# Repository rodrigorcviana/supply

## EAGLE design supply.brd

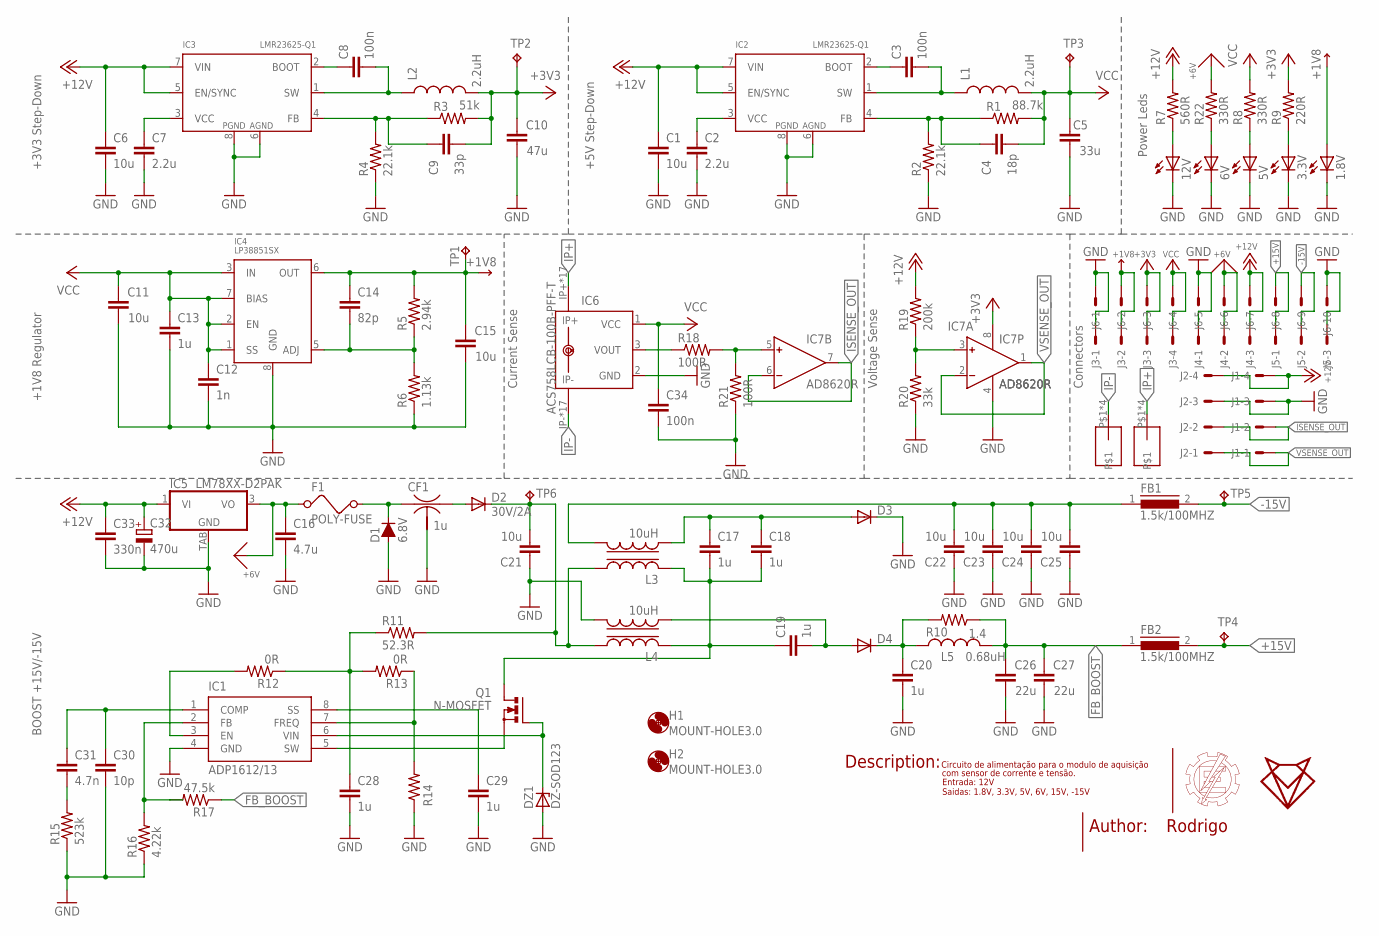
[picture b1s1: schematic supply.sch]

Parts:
1.8V, 3.3V, 5V, 6V, 12V: LEDCHIP-LED0805; CHIP-LED0805
C1, C6, C11, C15, C21, C22, C23, C24, C25: 10u; C1206
C2, C7: 2.2u; C0805
C3, C8: 100n; C0805
C4: 18p; C0805
C5: 33u; C1206
C9: 33p; C0805
C10: 47u; C1206
C12: 1n; C0805
C13, C17, C18: 1u; C0805
C14: 82p; C0805
C16: 4.7u; C0805
C19, C20, C28, C29: 1u; C0603
C26, C27: 22u; C1206
C30: 10p; C0603
C31: 4.7n; C0603
C32: 470u; 150CLZ-0810
C33: 330n; C0603
C34: 100n; C0603
CF1: 1u; NFM21C
D1: 6.8V; SMB
D2: 30V/2A; SOD123
D3, D4: DIODE-SOD323-W; SOD323-W
DZ1: DZ-SOD123; SOD123
F1: POLY-FUSE; 1210
FB1, FB2: 1.5k/100MHZ; 0603
H1, H2: MOUNT-HOLE3.0; 3,0
IC1: ADP1612/13; 8-MSOP
IC2, IC3: LMR23625-Q1; SO08
IC4: LP38851SX; TO263-7
IC5: LM78XX-D2PAK; TO263-3
IC6: ACS758LCB-100B-PFF-T; CB-PFF
IC7: AD8620R; SO8
J1: 22-05-7048-04; 7395-04
J2, J3: 22-27-2041-04; 6410-04
J4, J5: 22-27-2031-03; 6410-03
J6: 22-05-7108-10; 7395-10
L1, L2: 2.2uH; L-NR3010
L3, L4: 10uH; MSD7342-SMD
L5: 0.68uH; L2012C
Q1: N-MOSFET; SOT23
R1: 88.7k; R0603
R2, R4: 22.1k; R0603
R3: 51k; R0603
R5: 2.94k; R0603
R6: 1.13k; R0603
R7: 560R; R0603
R8, R22: 330R; R0603
R9: 220R; R0603
R10: 1.4; R0603
R11: 52.3R; R0603
R12, R13: 0R; R0603
R14: R-US_R0603; R0603
R15: 523k; R0603
R16: 4.22k; R0603
R17: 47.5k; R0603
R18, R21: 100R; R0805
R19: 200k; R0805
R20: 33k; R0805
TP1, TP2, TP3, TP4, TP5, TP6: TPPAD1-13; P1-13
U$3, U$4: SCREWCONECTOR

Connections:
+1V8: 1.8V.A, C14.1, C15.2, IC4.6 (OUT), J3.2, J6.2, R5.2, TP1.TP
+3V3: C9.2, C10.2, IC7.8 (V+), J3.3, J6.3, L2.P$2 (2), R3.2, R9.2, TP2.TP
+6V: C16.1, F1.1, IC5.3 (VO), J4.2, J6.6, R22.2
+12V: C1.1, C6.1, C32.+, C33.1, IC2.5 (EN/SYNC), IC2.7 (VIN), IC3.5 (EN/SYNC), IC3.7 (VIN), IC5.1 (VI), J1.4, J2.4, J4.3, J6.7, R7.2, R19.2
+15V: FB2.2, J5.1, J6.8, TP4.TP
-15V: FB1.2, J5.2, J6.9, TP5.TP
FB_BOOST: C26.2, C27.2, FB2.1, L5.2, R10.1, R17.1
GND: 1.8V.C, 3.3V.C, 5V.C, 6V.C, 12V.C, C1.2, C2.2, C5.1, C6.2, C7.2, C10.1, C11.1, C12.2, C13.2, C15.1, C16.2, C20.2, C21.1, C22.1, C23.1, C24.1, C25.1, C26.1, C27.1, C28.2, C29.2, C30.2, C32.-, C33.2, C34.2, CF1.2@1 (2), D1.2 (A), D3.C, DZ1.A, IC1.4 (GND), IC2.6 (AGND), IC2.8 (PGND), IC3.6 (AGND), IC3.8 (PGND), IC4.8 (GND), IC5.TAB (GND), IC6.2 (GND), IC7.4 (V-), J1.3, J2.3, J3.1, J4.1, J5.3, J6.1, J6.5, J6.10, L4.P$2 (2), R2.1, R4.1, R6.1, R14.1, R15.1, R16.1, R20.1, R21.1
IP+: IC6.IP+, IC6.IP+@2 (IP+), IC6.IP+@3 (IP+), IC6.IP+@4 (IP+), IC6.IP+@5 (IP+), IC6.IP+@6 (IP+), IC6.IP+@7 (IP+), IC6.IP+@8 (IP+), IC6.IP+@9 (IP+), IC6.IP+@10 (IP+), IC6.IP+@11 (IP+), IC6.IP+@12 (IP+), IC6.IP+@13 (IP+), IC6.IP+@14 (IP+), IC6.IP+@15 (IP+), IC6.IP+@16 (IP+), IC6.IP+@17 (IP+), U$4.P$1, U$4.P$2, U$4.P$3, U$4.P$4
IP-: IC6.IP-, IC6.IP-@2 (IP-), IC6.IP-@3 (IP-), IC6.IP-@4 (IP-), IC6.IP-@5 (IP-), IC6.IP-@6 (IP-), IC6.IP-@7 (IP-), IC6.IP-@8 (IP-), IC6.IP-@9 (IP-), IC6.IP-@10 (IP-), IC6.IP-@11 (IP-), IC6.IP-@12 (IP-), IC6.IP-@13 (IP-), IC6.IP-@14 (IP-), IC6.IP-@15 (IP-), IC6.IP-@16 (IP-), IC6.IP-@17 (IP-), U$3.P$1, U$3.P$2, U$3.P$3, U$3.P$4
ISENSE_OUT: IC7.6 (IN-), IC7.7 (OUT), J1.2, J2.2
unnamed: C3.1, IC2.2 (BOOT)
unnamed: C7.1, IC3.3 (VCC)
unnamed: C2.1, IC2.3 (VCC)
unnamed: C3.2, IC2.1 (SW), L1.P$1 (1)
unnamed: C4.1, IC2.4 (FB), R1.1, R2.2
unnamed: C8.1, IC3.2 (BOOT)
unnamed: C8.2, IC3.1 (SW), L2.P$1 (1)
unnamed: C9.1, IC3.4 (FB), R3.1, R4.2
unnamed: CF1.1, D1.1 (C), F1.2
unnamed: CF1.3, D2.A
unnamed: IC6.3 (VOUT), R18.1
unnamed: C14.2, IC4.5 (ADJ), R5.1, R6.2
unnamed: C31.2, R15.2
unnamed: C17.1, C18.1, D3.A, L3.P$4 (4)
unnamed: C19.2, D4.A, L4.P$4 (4)
unnamed: 12V.A, R7.1
unnamed: C20.1, D4.C, L5.1, R10.2
unnamed: 3.3V.A, R9.1
unnamed: 5V.A, R8.1
unnamed: C22.2, C23.2, C24.2, C25.2, FB1.1, L3.P$2 (2)
unnamed: IC1.5 (SW), Q1.2 (S)
unnamed: C28.1, R11.1, R12.1, R13.2
unnamed: IC1.3 (EN), R12.2
unnamed: IC1.2 (FB), R16.2, R17.2
unnamed: C29.1, IC1.8 (SS)
unnamed: IC1.7 (FREQ), R13.1, R14.2
unnamed: C30.1, C31.1, IC1.1 (COMP)
unnamed: 6V.A, R22.1
unnamed: DZ1.C, IC1.6 (VIN), Q1.1 (G)
unnamed: C21.2, D2.C, L3.P$1 (1), L4.P$1 (1), R11.2, TP6.TP
unnamed: C17.2, C18.2, C19.1, L3.P$3 (3), L4.P$3 (3), Q1.3 (D)
unnamed: IC7.3 (IN+), R19.1, R20.2
unnamed: IC7.5 (IN+), R18.2, R21.2
VCC: C4.2, C5.2, C11.2, C12.1, C13.1, C34.1, IC4.1 (SS), IC4.2 (EN), IC4.3 (IN), IC4.7 (BIAS), IC6.1 (VCC), J3.4, J6.4, L1.P$2 (2), R1.2, R8.2, TP3.TP
VSENSE_OUT: IC7.1 (OUT), IC7.2 (IN-), J1.1, J2.1

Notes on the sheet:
BOOST +15V/-15V
+1V8 Regulator
+3V3 Step-Down
+5V Step-Down
Power Leds
Current Sense
Voltage Sense
Connectors
Circuito de alimentação para o modulo de aquisição
Entrada: 12V Saidas: 1.8V, 3.3V, 5V, 6V, 15V, -15V
Description:
Author:
Rodrigo
com sensor de corrente e tensão.

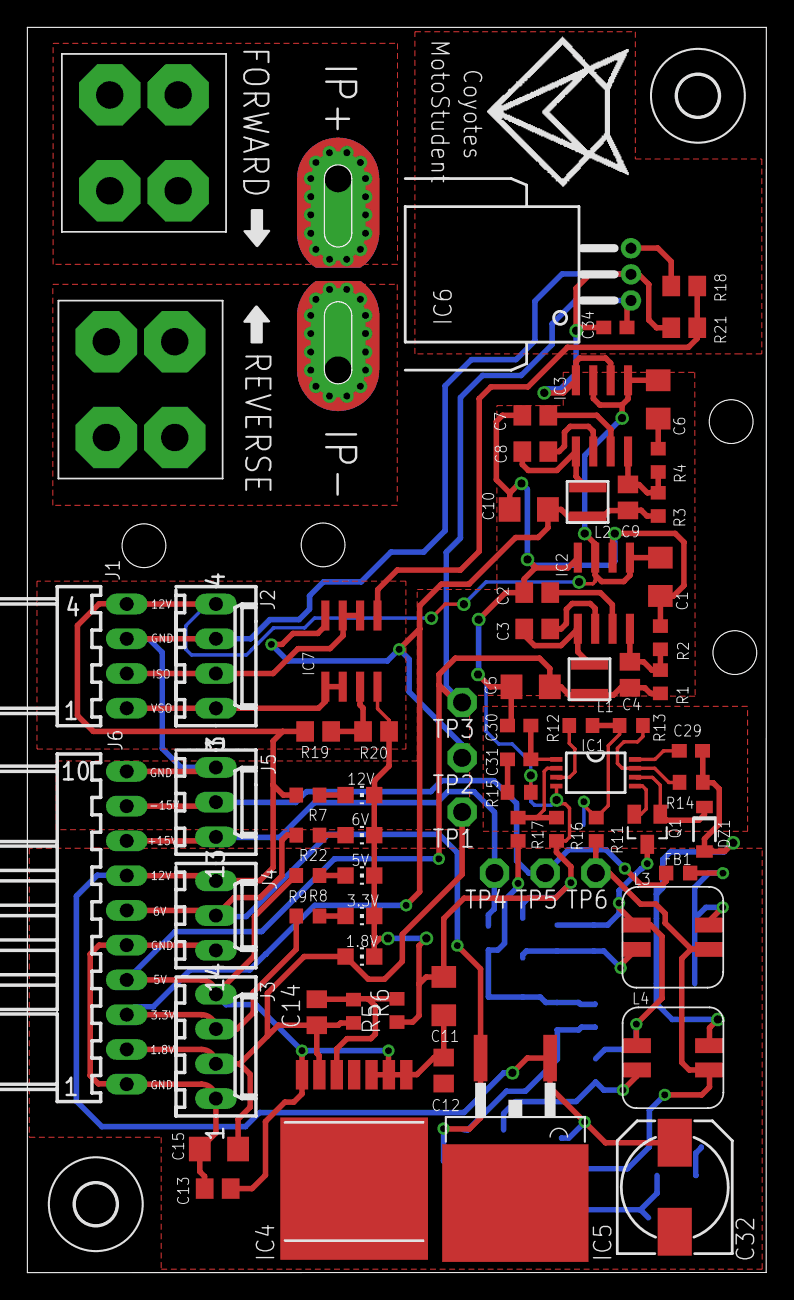
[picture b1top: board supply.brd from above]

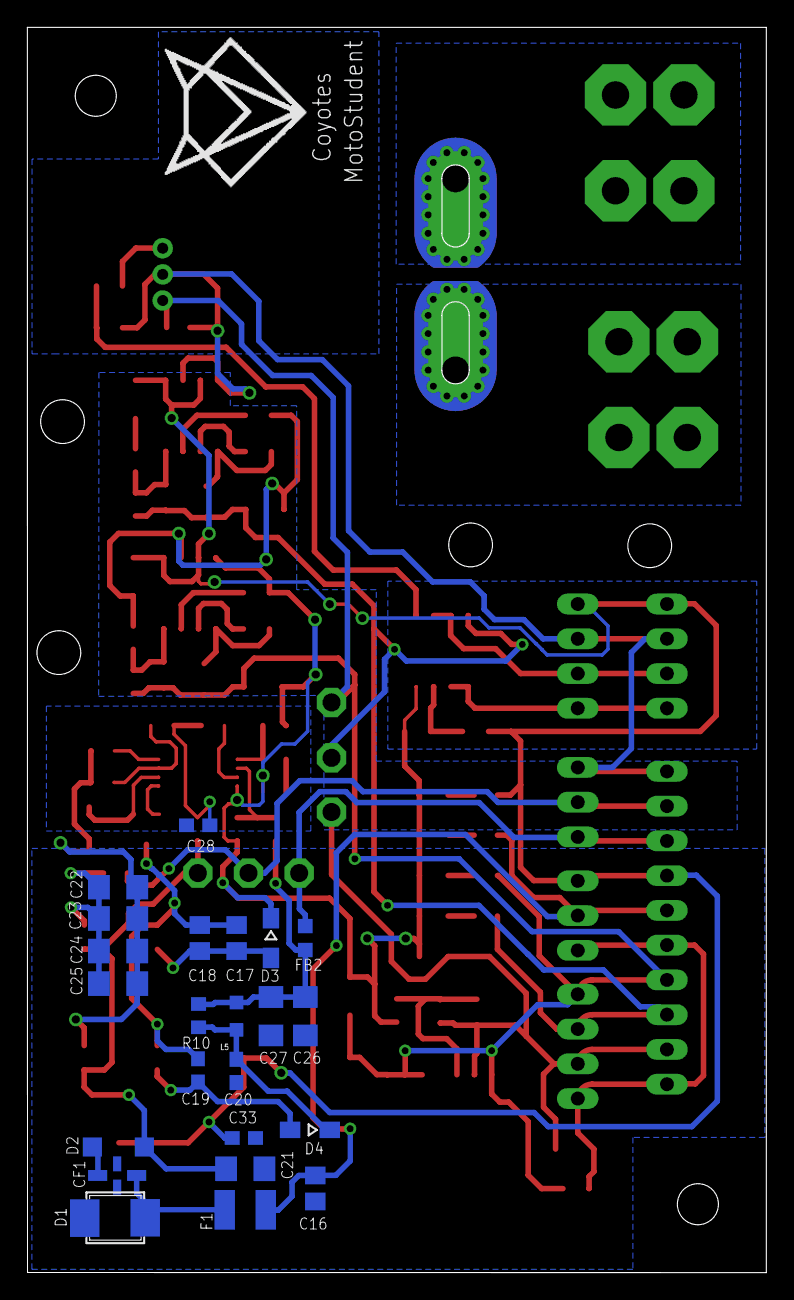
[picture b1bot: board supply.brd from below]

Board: 2 copper layers, 54.0 x 91.0 mm, 103 parts (24 on the bottom side), 46 nets.

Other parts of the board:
U$11, U$12: LOGO_COYOTES
U$13, U$14: SETA_DIREITA

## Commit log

2021-04-13 update files
